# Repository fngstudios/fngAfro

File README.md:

# fngAfro

fngAfro atmega8 based brushless dc motor speed controller TGY compatible.  
Prototype working, pcb layout will change in near future.  

## Features
*Uses max662 IC for fet driver supply.  
*Compatible with most high current n channel mosfets (d2pack).  
*40A rated.  
*Comp-PWM.  
*Regenerative breaking.  
*TGY compatible.  
*PPM/I2C/ input.  
*HV version for voltage input above 30V (7S).  

## Images

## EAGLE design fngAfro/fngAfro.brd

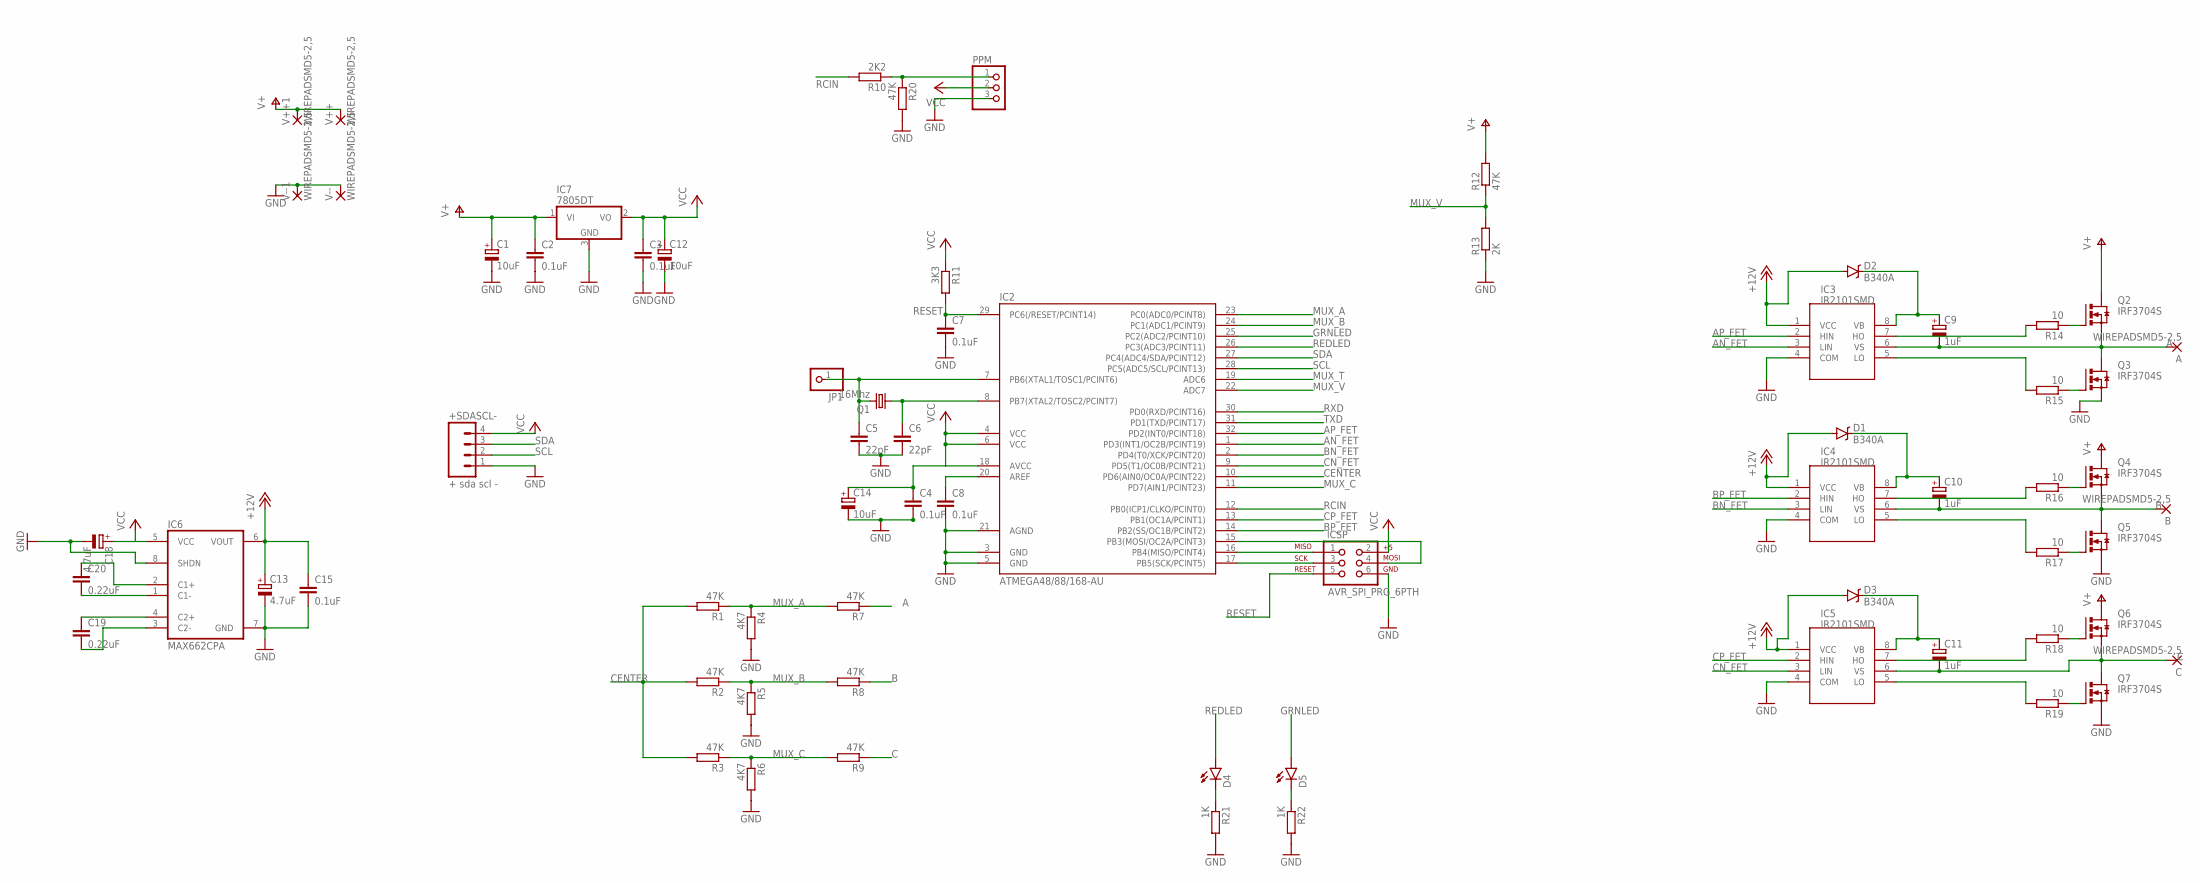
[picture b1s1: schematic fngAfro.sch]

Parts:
+SDASCL-: + sda scl -; 1X04_LOCK
A: WIREPADSMD5-2,5; 5-2,5
B: WIREPADSMD5-2,5; 5-2,5
C: WIREPADSMD5-2,5; 5-2,5
C1: 10uF; CT3216
C2, C3, C4, C7, C8, C15: 0.1uF; C1206K
C5, C6: 22pF; C1206K
C9, C10, C11: 1uF; B/3528-21R
C12, C14: 10uF; A/3216-18W
C13, C18: 4.7uF; CT3216
C19, C20: 0.22uF; C1206K
D1, D2, D3: B340A; SMA-DIODE
D4, D5: LED-FKIT-1206; FKIT-LED-1206
IC2: ATMEGA48/88/168-AU; TQFP32-08
IC3, IC4, IC5: IR2101SMD; SO08
IC6: MAX662CPA; SO08
IC7: 7805DT; TO252
ICSP: AVR_SPI_PRG_6PTH; 2X3
JP1: PINHD-1X1; 1X01
PPM: PINHD-1X3; 1X03
Q1: 16Mhz; HC49U70
Q2, Q3, Q4, Q5, Q6, Q7: IRF3704S; D2PACK
R1, R2, R3, R7, R8, R9, R12: 47K; M0805
R4, R5, R6: 4K7; M0805
R10: 2K2; M1206
R11: 3K3; M1206
R13: 2K; M0805
R14, R15, R16, R17, R18, R19: 10; M0805
R20: 47K; M1206
R21, R22: 1K; M0805
V++, V++1: WIREPADSMD5-2,5; 5-2,5
V--, V--1: WIREPADSMD5-2,5; 5-2,5

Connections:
+12V: C13.+, C15.1, D1.A, D2.A, D3.A, IC3.1 (VCC), IC4.1 (VCC), IC5.1 (VCC), IC6.6 (VOUT)
A: A.1, C9.-, IC3.6 (VS), Q2.3 (S), Q3.2 (D), R7.1
AN_FET: IC2.1 (PD3(INT1/OC2B/PCINT19)), IC3.3 (LIN)
AP_FET: IC2.32 (PD2(INT0/PCINT18)), IC3.2 (HIN)
B: B.1, C10.-, IC4.6 (VS), Q4.3 (S), Q5.2 (D), R8.1
BN_FET: IC2.2 (PD4(T0/XCK/PCINT20)), IC4.3 (LIN)
BP_FET: IC2.14 (PB2(SS/OC1B/PCINT2)), IC4.2 (HIN)
C: C.1, C11.-, IC5.6 (VS), Q6.3 (S), Q7.2 (D), R9.1
CENTER: IC2.10 (PD6(AIN0/OC0A/PCINT22)), R1.2, R2.2, R3.2
CN_FET: IC2.9 (PD5(T1/OC0B/PCINT21)), IC5.3 (LIN)
CP_FET: IC2.13 (PB1(OC1A/PCINT1)), IC5.2 (HIN)
GND: +SDASCL-.1, C1.-, C2.2, C3.2, C4.2, C5.2, C6.2, C7.2, C8.2, C12.-, C13.-, C14.-, C15.2, C18.-, IC2.3 (GND), IC2.5 (GND), IC2.21 (AGND), IC3.4 (COM), IC4.4 (COM), IC5.4 (COM), IC6.7 (GND), IC6.8 (SHDN), IC7.3 (GND), ICSP.6, PPM.3, Q3.3 (S), Q5.3 (S), Q7.3 (S), R4.2, R5.2, R6.2, R13.1, R20.2, R21.2, R22.2, V--.1, V--1.1
GRNLED: D5.A, IC2.25 (PC2(ADC2/PCINT10))
MUX_A: IC2.23 (PC0(ADC0/PCINT8)), R1.1, R4.1, R7.2
MUX_B: IC2.24 (PC1(ADC1/PCINT9)), R2.1, R5.1, R8.2
MUX_C: IC2.11 (PD7(AIN1/PCINT23)), R3.1, R6.1, R9.2
MUX_T: IC2.19 (ADC6)
MUX_V: IC2.22 (ADC7), R12.1, R13.2
unnamed: IC2.17 (PB5(SCK/PCINT5)), ICSP.3
unnamed: IC2.16 (PB4(MISO/PCINT4)), ICSP.1
unnamed: IC2.15 (PB3(MOSI/OC2A/PCINT3)), ICSP.4
unnamed: Q2.1 (G), R14.1
unnamed: IC4.7 (HO), R16.2
unnamed: Q3.1 (G), R15.1
unnamed: IC4.5 (LO), R17.2
unnamed: IC5.7 (HO), R18.2
unnamed: Q4.1 (G), R16.1
unnamed: IC5.5 (LO), R19.2
unnamed: Q5.1 (G), R17.1
unnamed: Q6.1 (G), R18.1
unnamed: Q7.1 (G), R19.1
unnamed: C19.1, IC6.4 (C2+)
unnamed: IC3.7 (HO), R14.2
unnamed: IC3.5 (LO), R15.2
unnamed: C19.2, IC6.3 (C2-)
unnamed: D4.C, R21.1
unnamed: C6.1, IC2.8 (PB7(XTAL2/TOSC2/PCINT7)), Q1.1
unnamed: C5.1, IC2.7 (PB6(XTAL1/TOSC1/PCINT6)), JP1.1, Q1.2
unnamed: C8.1, IC2.20 (AREF)
unnamed: PPM.1, R10.1, R20.1
unnamed: D5.C, R22.1
unnamed: C20.2, IC6.1 (C1-)
unnamed: C20.1, IC6.2 (C1+)
RCIN: IC2.12 (PB0(ICP1/CLKO/PCINT0)), R10.2
REDLED: D4.A, IC2.26 (PC3(ADC3/PCINT11))
RESET: C7.1, IC2.29 (PC6(/RESET/PCINT14)), ICSP.5, R11.2
RXD: IC2.30 (PD0(RXD/PCINT16))
SCL: +SDASCL-.2, IC2.28 (PC5(ADC5/SCL/PCINT13))
SDA: +SDASCL-.3, IC2.27 (PC4(ADC4/SDA/PCINT12))
TXD: IC2.31 (PD1(TXD/PCINT17))
V+: C1.+, C2.1, IC7.1 (VI), Q2.2 (D), Q4.2 (D), Q6.2 (D), R12.2, V++.1, V++1.1
VBA: C9.+, D2.C, IC3.8 (VB)
VBB: C10.+, D1.C, IC4.8 (VB)
VBC: C11.+, D3.C, IC5.8 (VB)
VCC: +SDASCL-.4, C3.1, C4.1, C12.+, C14.+, C18.+, IC2.4 (VCC), IC2.6 (VCC), IC2.18 (AVCC), IC6.5 (VCC), IC7.2 (VO), ICSP.2, PPM.2, R11.1

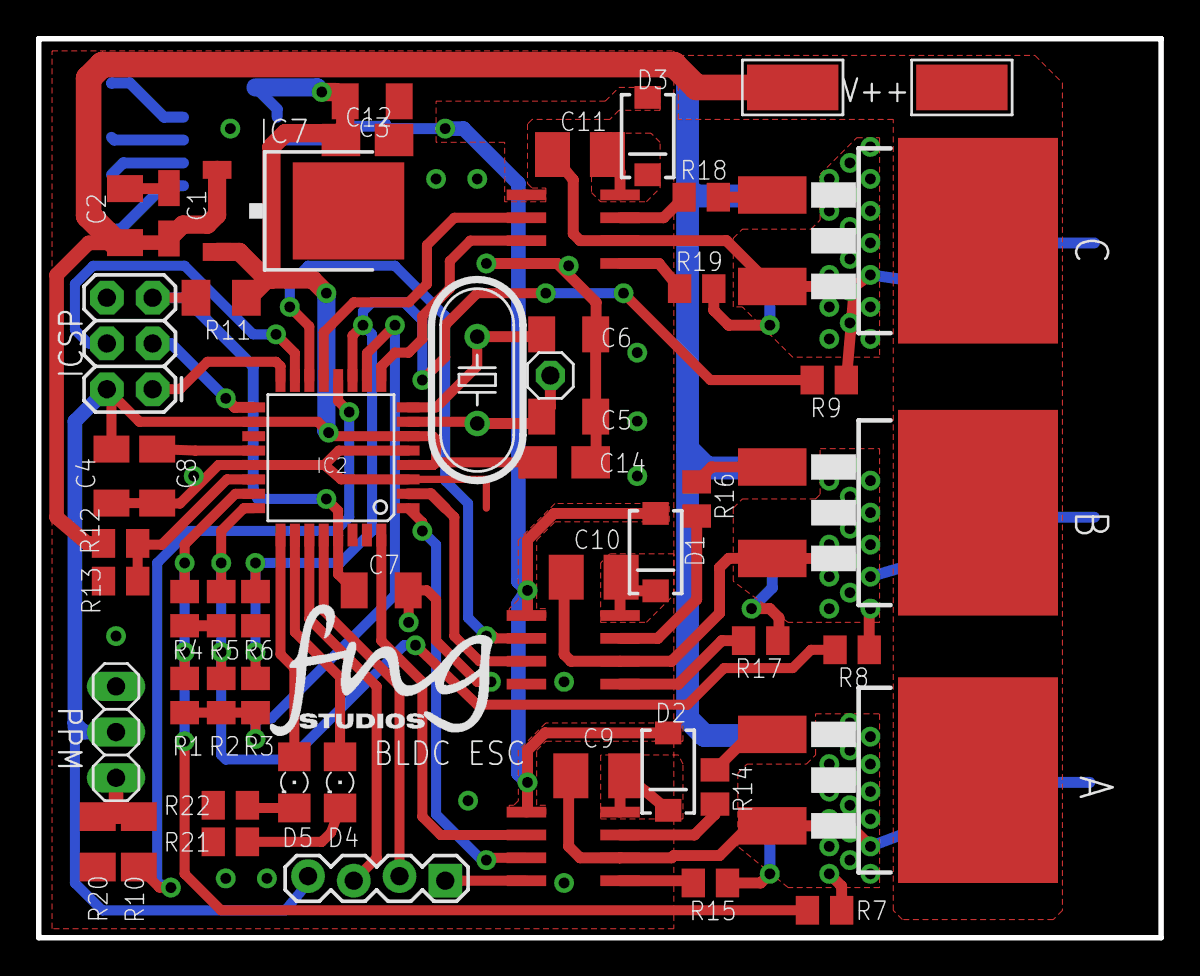
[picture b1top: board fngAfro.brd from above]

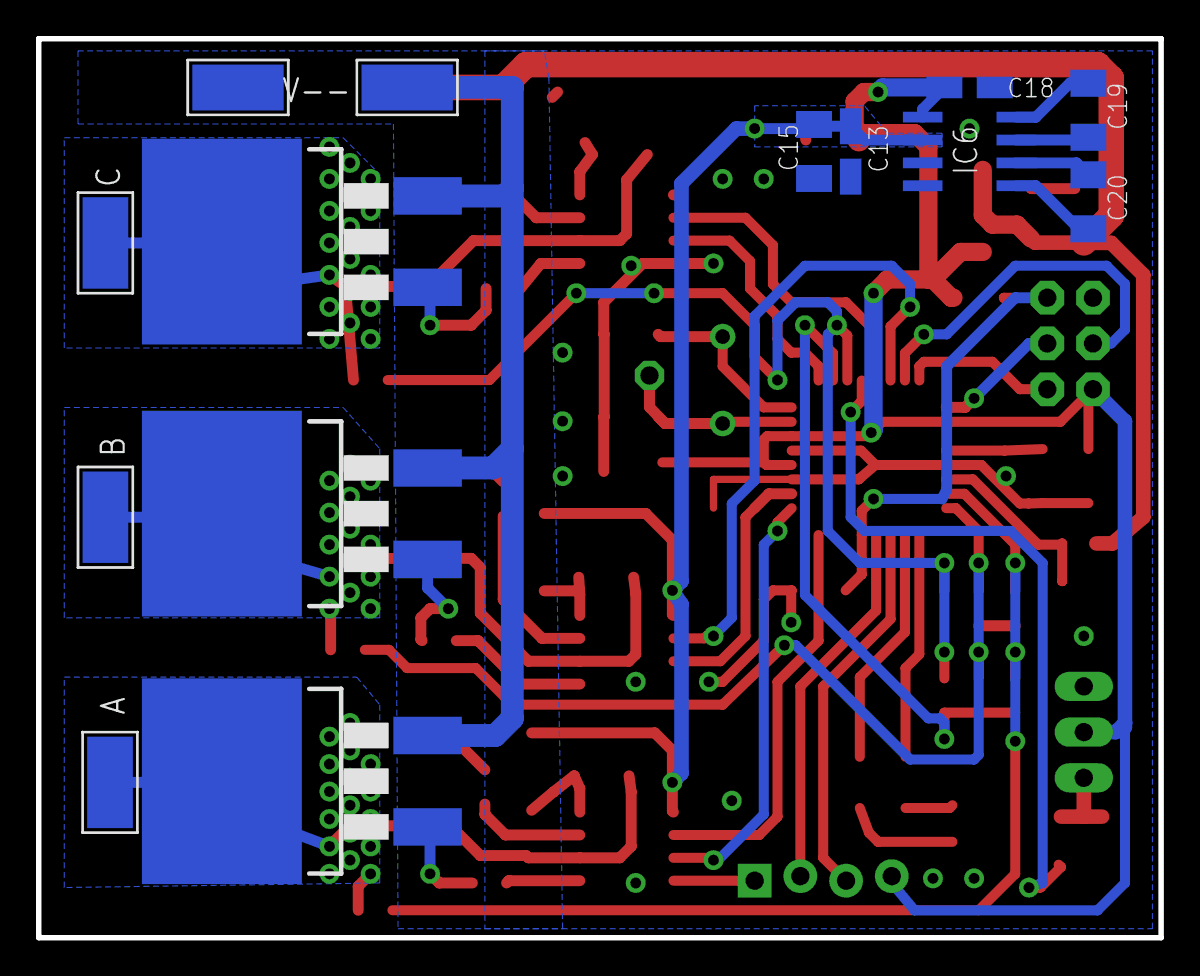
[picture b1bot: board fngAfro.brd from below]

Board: 2 copper layers, 62.4 x 49.9 mm, 70 parts (14 on the bottom side), 52 nets.

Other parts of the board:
U$2: LOGOFNGNAME1

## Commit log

2016-07-02 fngAgro
    BLDC ESC fngAfro, compratible with simonK afroHV
2016-12-18 Release
2016-12-18 Readme

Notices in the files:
parts and their libraries:
SparkFun-DiscreteSemi: Licensing: Creative Commons ShareAlike 4.0 International - https://creativecommons.org/licenses/by-sa/4.0
